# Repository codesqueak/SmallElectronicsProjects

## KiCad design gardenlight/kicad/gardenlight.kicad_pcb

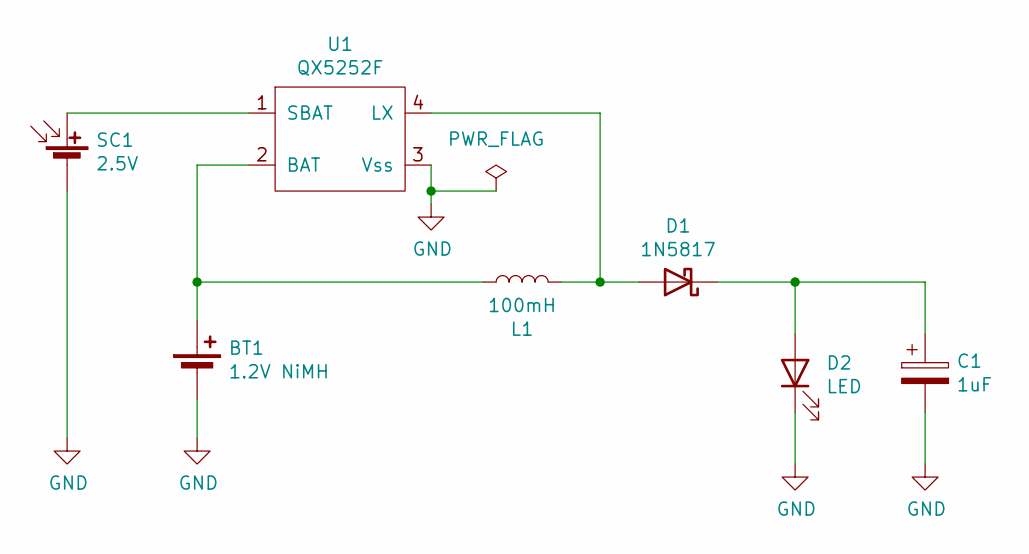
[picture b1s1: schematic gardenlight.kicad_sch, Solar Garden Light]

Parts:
BT1: 1.2V NiMH; JST_PH_B2B-PH-K_1x02_P2.00mm_Vertical
C1: 1uF; CP_Radial_D4.0mm_P1.50mm
D1: 1N5817; D_DO-41_SOD81_P10.16mm_Horizontal
D2: LED; LED_D5.0mm
L1: 100mH; L_Axial_L6.6mm_D2.7mm_P10.16mm_Horizontal_Vishay_IM-2
SC1: 2.5V; JST_PH_B2B-PH-K_1x02_P2.00mm_Vertical
U1: QX5252F

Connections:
GND: BT1.2 (-), C1.2, D2.1 (K), SC1.2 (-), U1.3 (Vss)
unnamed: BT1.1 (+), L1.1, U1.2 (BAT)
unnamed: C1.1, D1.1 (K), D2.2 (A)
unnamed: D1.2 (A), L1.2, U1.4 (LX)
unnamed: SC1.1 (+), U1.1 (SBAT)

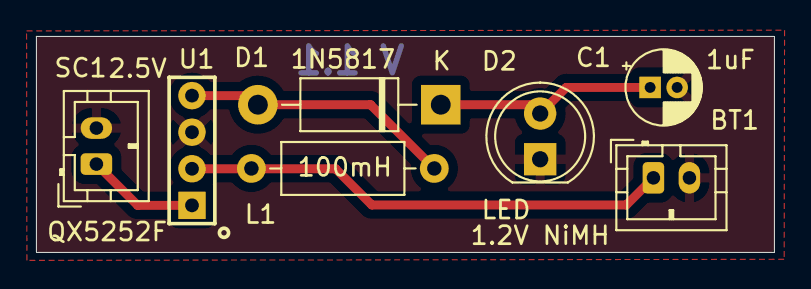
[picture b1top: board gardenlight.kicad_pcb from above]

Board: 2 copper layers, 41.0 x 12.0 mm, 7 parts (0 on the bottom side), 5 nets.

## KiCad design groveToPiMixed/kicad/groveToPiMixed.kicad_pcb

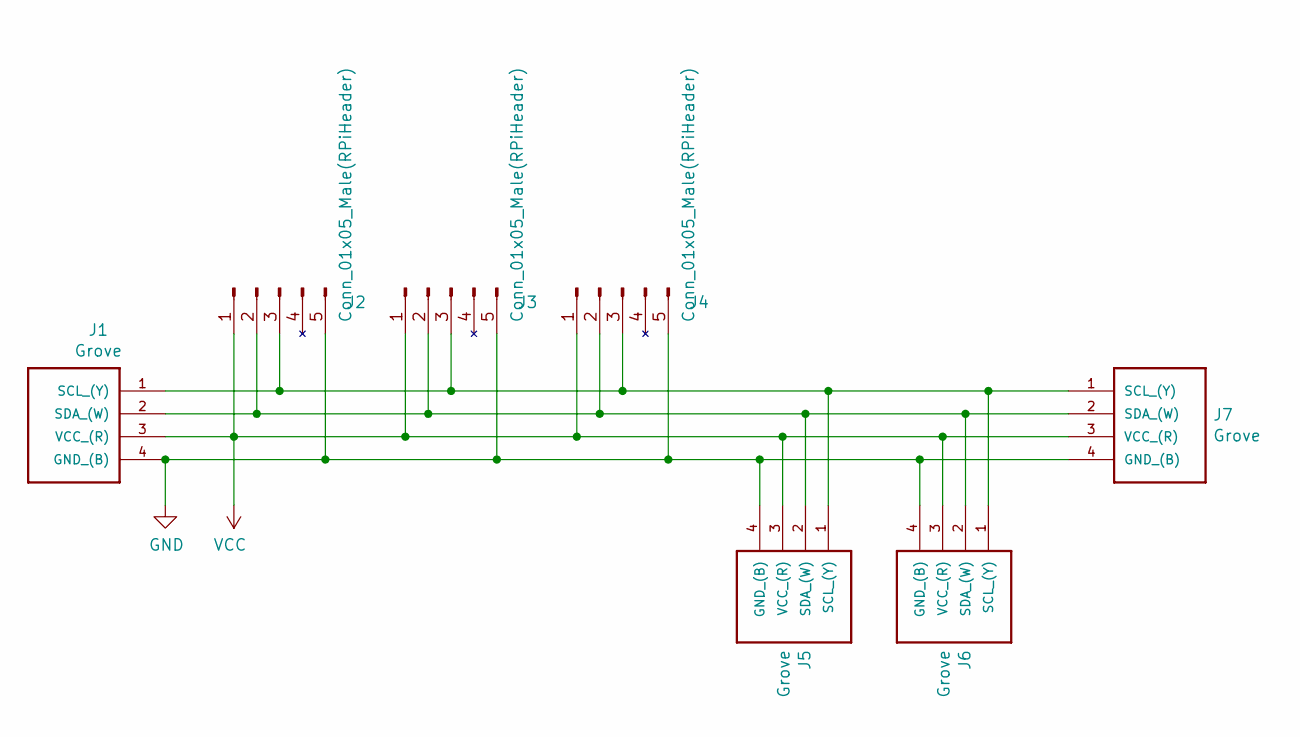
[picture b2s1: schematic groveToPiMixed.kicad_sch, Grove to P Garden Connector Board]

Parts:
J1, J5, J6, J7: Grove; GroveConnector
J2, J3, J4: Conn_01x05_Male(RPiHeader); PinSocket_1x05_P2.54mm_Vertical

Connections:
GND: J1.4 (GND_(B)), J2.5, J3.5, J4.5, J5.4 (GND_(B)), J6.4 (GND_(B)), J7.4 (GND_(B))
unnamed: J1.1 (SCL_(Y)), J2.3, J3.3, J4.3, J5.1 (SCL_(Y)), J6.1 (SCL_(Y)), J7.1 (SCL_(Y))
unnamed: J1.2 (SDA_(W)), J2.2, J3.2, J4.2, J5.2 (SDA_(W)), J6.2 (SDA_(W)), J7.2 (SDA_(W))
VCC: J1.3 (VCC_(R)), J2.1, J3.1, J4.1, J5.3 (VCC_(R)), J6.3 (VCC_(R)), J7.3 (VCC_(R))

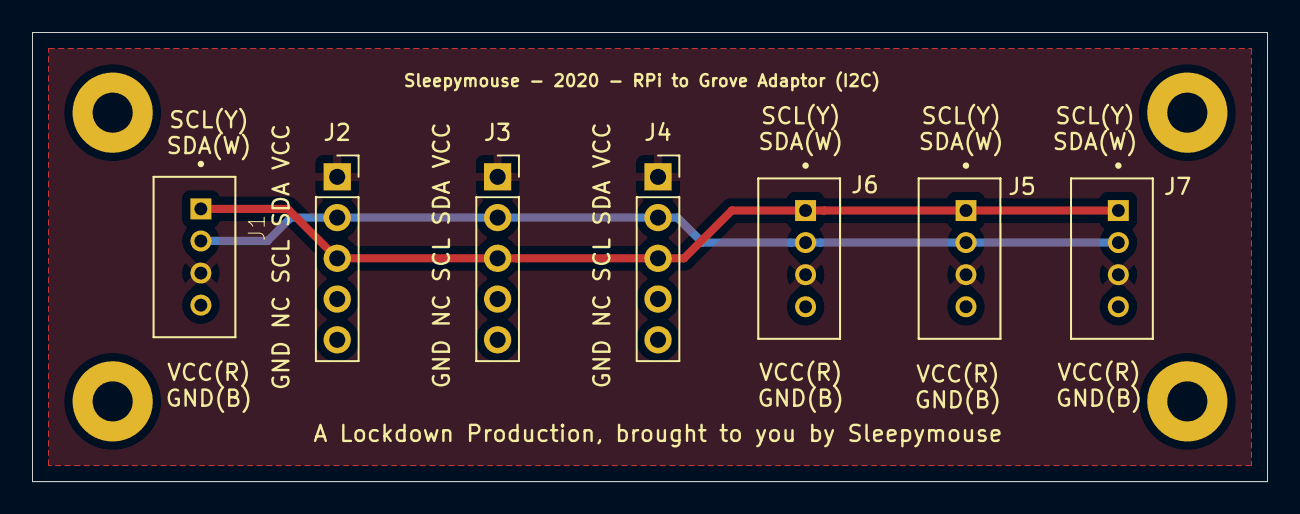
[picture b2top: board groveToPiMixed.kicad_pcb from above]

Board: 2 copper layers, 77.0 x 28.0 mm, 7 parts (0 on the bottom side), 4 nets.
